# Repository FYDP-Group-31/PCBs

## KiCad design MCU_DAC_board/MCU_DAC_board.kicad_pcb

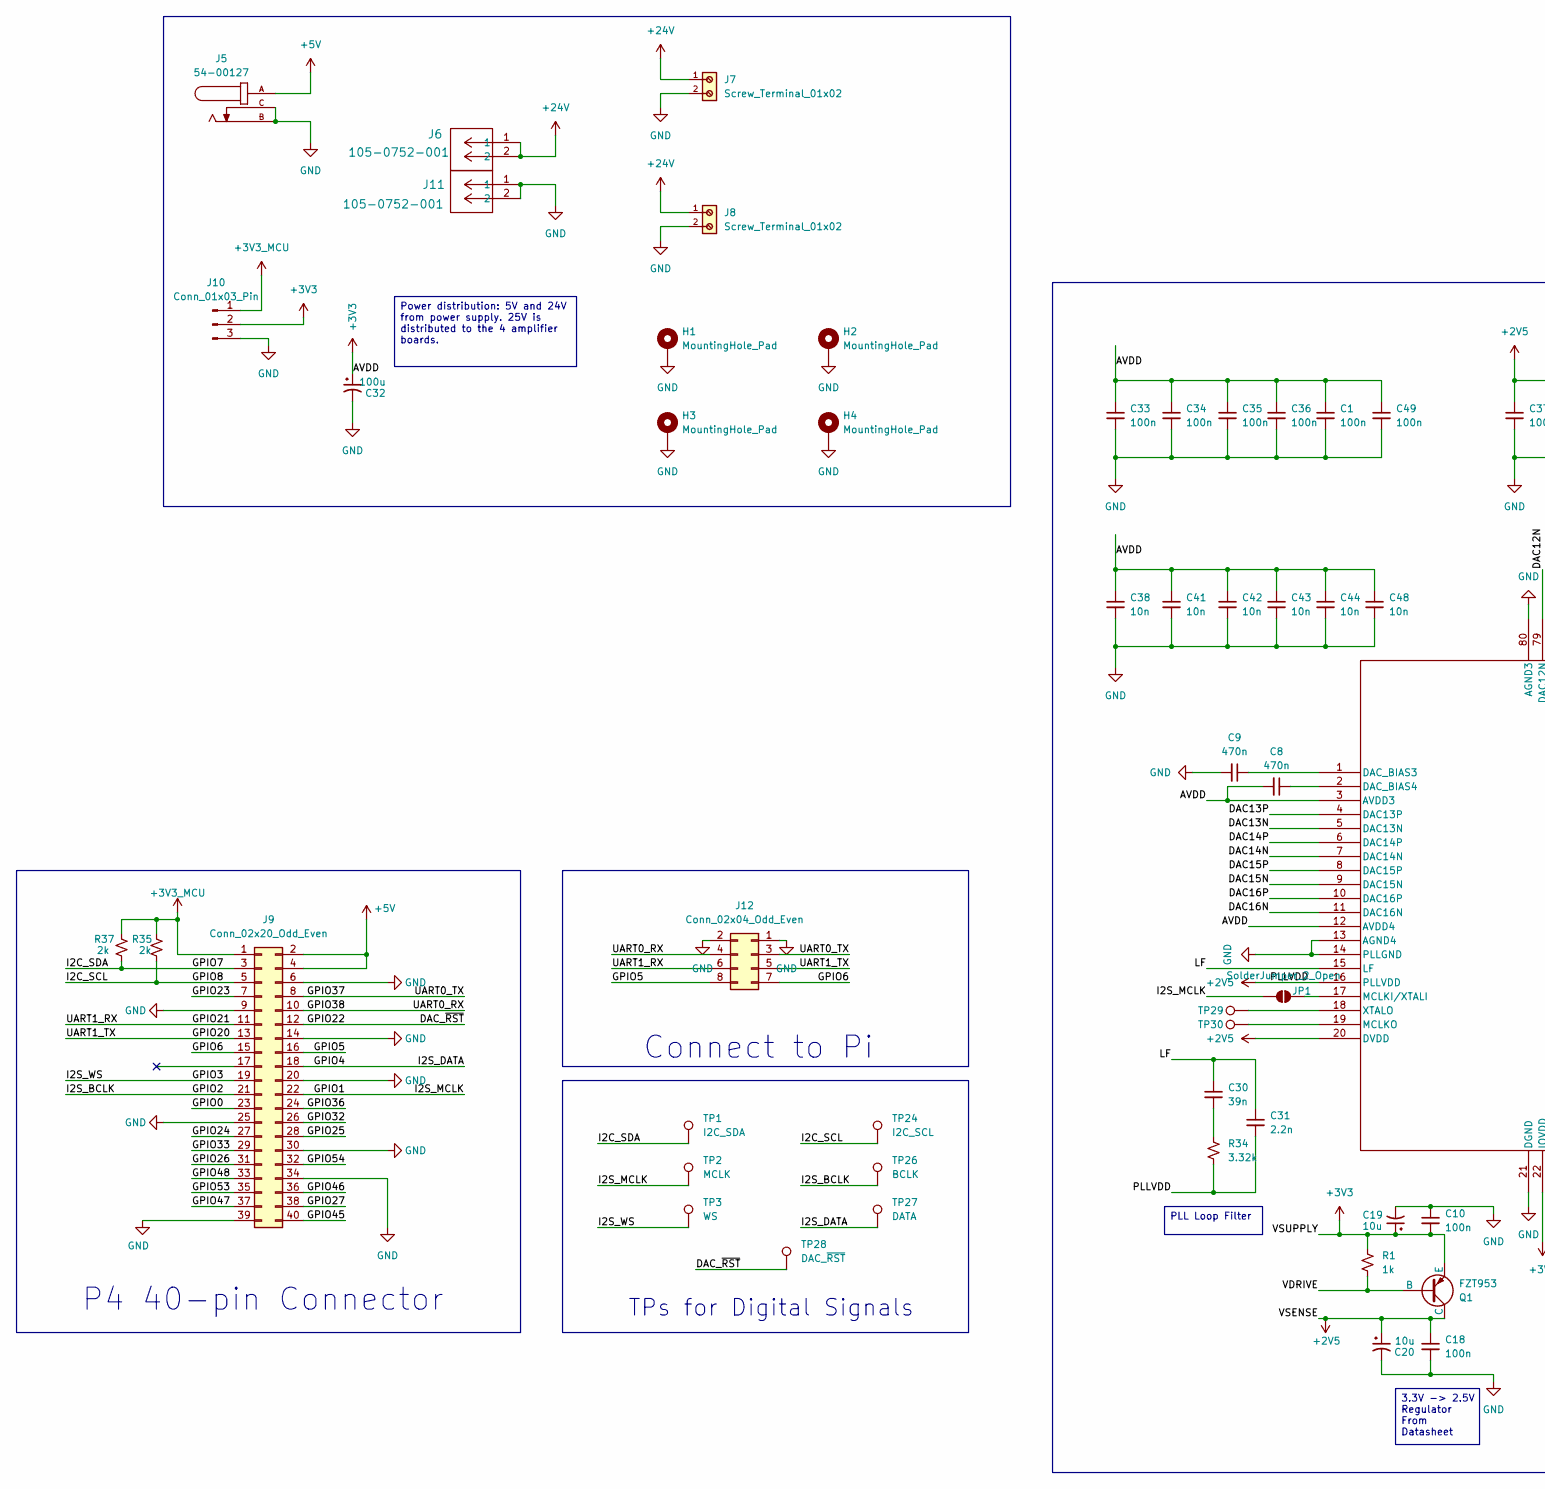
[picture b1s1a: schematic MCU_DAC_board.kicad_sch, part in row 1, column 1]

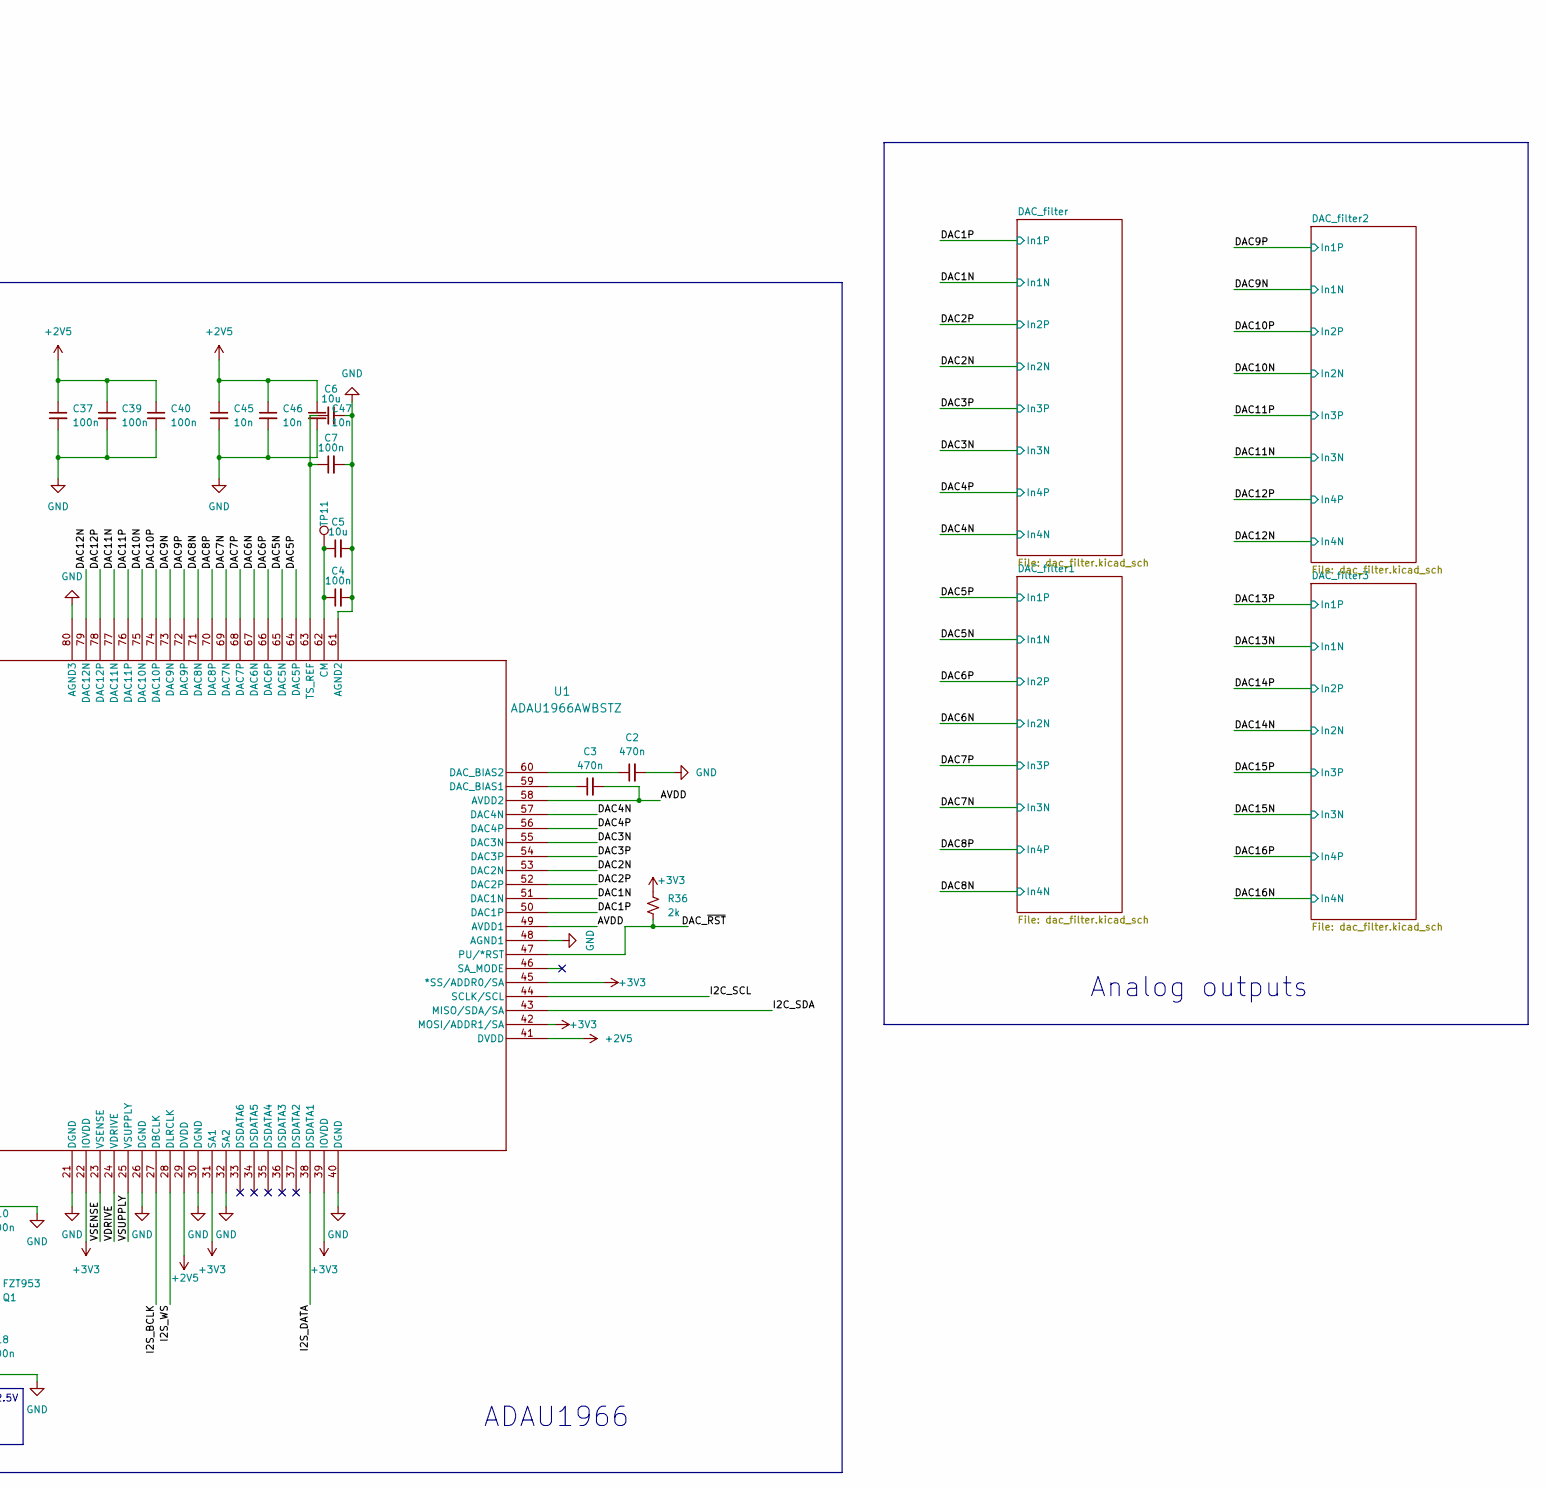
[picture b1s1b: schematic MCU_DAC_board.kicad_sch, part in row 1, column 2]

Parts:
C1, C4, C7, C10, C18, C33, C34, C35, C36, C37, C39, C40, C49: 100n; C_0603_1608Metric_Pad1.08x0.95mm_HandSolder
C2, C3, C8, C9: 470n; C_0603_1608Metric_Pad1.08x0.95mm_HandSolder
C5, C6: 10u; C_0805_2012Metric_Pad1.18x1.45mm_HandSolder
C19, C20: 10u; CP_Elec_4x4.5
C30: 39n; C_0805_2012Metric_Pad1.18x1.45mm_HandSolder
C31: 2.2n; C_0805_2012Metric_Pad1.18x1.45mm_HandSolder
C32: 100u; CP_Radial_D6.3mm_P2.50mm
C38, C41, C42, C43, C44, C45, C46, C47, C48: 10n; C_0603_1608Metric_Pad1.08x0.95mm_HandSolder
H1, H2, H3, H4: MountingHole_Pad; MountingHole_2.7mm_M2.5_DIN965_Pad_TopBottom
J5: 54-00127; TENSILITY_54-00127; PARTREV A
J6, J11: 105-0752-001; CONN_0752-001
J7, J8: Screw_Terminal_01x02; 691137710002
J9: Conn_02x20_Odd_Even; PinSocket_2x20_P2.54mm_Vertical_SMD
J10: Conn_01x03_Pin; PinHeader_1x03_P2.54mm_Vertical
J12: Conn_02x04_Odd_Even; PinSocket_2x04_P2.54mm_Vertical
JP1: SolderJumper_2_Open; R_0201_0603Metric_Pad0.64x0.40mm_HandSolder
Q1: FZT953; SOT-223-3_TabPin2
R1: 1k; R_0805_2012Metric_Pad1.20x1.40mm_HandSolder
R34: 3.32k; R_0805_2012Metric_Pad1.20x1.40mm_HandSolder
R35, R36, R37: 2k; R_0805_2012Metric_Pad1.20x1.40mm_HandSolder
TP1: I2C_SDA; TP_1.8x1mm
TP2: MCLK; TP_1.8x1mm
TP3: WS; TP_1.8x1mm
TP11: CM; TP_1.8x1mm
TP24: I2C_SCL; TP_1.8x1mm
TP26: BCLK; TP_1.8x1mm
TP27: DATA; TP_1.8x1mm
TP28: DAC_~{RST}; TP_1.8x1mm
TP29: XTALO; TP_1.8x1mm
TP30: MCLKO; TP_1.8x1mm
U1: ADAU1966AWBSTZ; ST_80_2_ADI

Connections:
+2V5: C18.1, C20.1, C31.2, C37.1, C39.1, C40.1, C45.1, C46.1, C47.1, Q1.2 (C), R34.2, U1.16 (PLLVDD), U1.20 (DVDD), U1.23 (VSENSE), U1.29 (DVDD), U1.41 (DVDD)
+3V3: C1.1, C3.2, C8.2, C10.2, C19.1, C32.1, C33.1, C34.1, C35.1, C36.1, C38.1, C41.1, C42.1, C43.1, C44.1, C48.1, C49.1, J10.2, Q1.3 (E), R1.1, R36.1, U1.3 (AVDD3), U1.12 (AVDD4), U1.22 (IOVDD), U1.25 (VSUPPLY), U1.31 (SA1), U1.39 (IOVDD), U1.42 (MOSI/ADDR1/SA), U1.45 (*SS/ADDR0/SA), U1.49 (AVDD1), U1.58 (AVDD2)
+3V3_MCU: J9.1, J10.1, R35.1, R37.1
+5V: J5.A, J9.2, J9.4
+24V: J6.1, J6.2, J7.1, J8.1
/DAC1N: U1.51 (DAC1N); also elsewhere on the board
/DAC1P: U1.50 (DAC1P); also elsewhere on the board
/DAC2N: U1.53 (DAC2N); also elsewhere on the board
/DAC2P: U1.52 (DAC2P); also elsewhere on the board
/DAC3N: U1.55 (DAC3N); also elsewhere on the board
/DAC3P: U1.54 (DAC3P); also elsewhere on the board
/DAC4N: U1.57 (DAC4N); also elsewhere on the board
/DAC4P: U1.56 (DAC4P); also elsewhere on the board
/DAC5N: U1.65 (DAC5N); also elsewhere on the board
/DAC5P: U1.64 (DAC5P); also elsewhere on the board
/DAC6N: U1.67 (DAC6N); also elsewhere on the board
/DAC6P: U1.66 (DAC6P); also elsewhere on the board
/DAC7N: U1.69 (DAC7N); also elsewhere on the board
/DAC7P: U1.68 (DAC7P); also elsewhere on the board
/DAC8N: U1.71 (DAC8N); also elsewhere on the board
/DAC8P: U1.70 (DAC8P); also elsewhere on the board
/DAC9N: U1.73 (DAC9N); also elsewhere on the board
/DAC9P: U1.72 (DAC9P); also elsewhere on the board
/DAC10N: U1.75 (DAC10N); also elsewhere on the board
/DAC10P: U1.74 (DAC10P); also elsewhere on the board
/DAC11N: U1.77 (DAC11N); also elsewhere on the board
/DAC11P: U1.76 (DAC11P); also elsewhere on the board
/DAC12N: U1.79 (DAC12N); also elsewhere on the board
/DAC12P: U1.78 (DAC12P); also elsewhere on the board
/DAC13N: U1.5 (DAC13N); also elsewhere on the board
/DAC13P: U1.4 (DAC13P); also elsewhere on the board
/DAC14N: U1.7 (DAC14N); also elsewhere on the board
/DAC14P: U1.6 (DAC14P); also elsewhere on the board
/DAC15N: U1.9 (DAC15N); also elsewhere on the board
/DAC15P: U1.8 (DAC15P); also elsewhere on the board
/DAC16N: U1.11 (DAC16N); also elsewhere on the board
/DAC16P: U1.10 (DAC16P); also elsewhere on the board
/DAC_~RST: J9.12, R36.2, TP28.1, U1.47 (PU/*RST)
/GPIO0: J9.23
/GPIO1: J9.22, JP1.1 (A), TP2.1
/GPIO2: J9.21, TP26.1, U1.27 (DBCLK)
/GPIO3: J9.19, TP3.1, U1.28 (DLRCLK)
/GPIO4: J9.18, TP27.1, U1.38 (DSDATA1)
/GPIO5: J9.16, J12.8
/GPIO6: J9.15, J12.7
/GPIO7: J9.3, R37.2, TP1.1, U1.43 (MISO/SDA/SA)
/GPIO8: J9.5, R35.2, TP24.1, U1.44 (SCLK/SCL)
/GPIO20: J9.13, J12.5
/GPIO21: J9.11, J12.6
/GPIO23: J9.7
/GPIO24: J9.27
/GPIO25: J9.28
/GPIO26: J9.31
/GPIO27: J9.38
/GPIO32: J9.26
/GPIO33: J9.29
/GPIO36: J9.24
/GPIO37: J9.8, J12.3
/GPIO38: J9.10, J12.4
/GPIO45: J9.40
/GPIO46: J9.36
/GPIO47: J9.37
/GPIO48: J9.33
/GPIO53: J9.35
/GPIO54: J9.32
/LF: C30.1, C31.1, U1.15 (LF)
/VDRIVE: Q1.1 (B), R1.2, U1.24 (VDRIVE)
GND: C1.2, C2.2, C4.2, C5.2, C6.2, C7.2, C9.2, C10.1, C18.2, C19.2, C20.2, C32.2, C33.2, C34.2, C35.2, C36.2, C37.2, C38.2, C39.2, C40.2, C41.2, C42.2, C43.2, C44.2, C45.2, C46.2, C47.2, C48.2, C49.2, H1.1, H2.1, H3.1, H4.1, J5.B, J5.C, J7.2, J8.2, J9.6, J9.9, J9.14, J9.20, J9.25, J9.30, J9.34, J9.39, J10.3, J11.1, J11.2, J12.1, J12.2, U1.13 (AGND4), U1.14 (PLLGND), U1.21 (DGND), U1.26 (DGND), U1.30 (DGND), U1.32 (SA2), U1.40 (DGND), U1.48 (AGND1), U1.61 (AGND2), U1.80 (AGND3)
unnamed: C30.2, R34.1
unnamed: JP1.2 (B), U1.17 (MCLKI/XTALI)
unnamed: C4.1, C5.1, TP11.1, U1.62 (CM)
unnamed: C3.1, U1.59 (DAC_BIAS1)
unnamed: C2.1, U1.60 (DAC_BIAS2)
unnamed: C9.1, U1.1 (DAC_BIAS3)
unnamed: C8.1, U1.2 (DAC_BIAS4)
unnamed: TP30.1, U1.19 (MCLKO)
unnamed: C6.1, C7.1, U1.63 (TS_REF)
unnamed: TP29.1, U1.18 (XTALO)

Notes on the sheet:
Connect to Pi
P4 40-pin Connector
Analog outputs
ADAU1966
TPs for Digital Signals
3.3V -> 2.5V Regulator From Datasheet
PLL Loop Filter
Power distribution: 5V and 24V from power supply. 25V is distributed to the 4 amplifier boards.

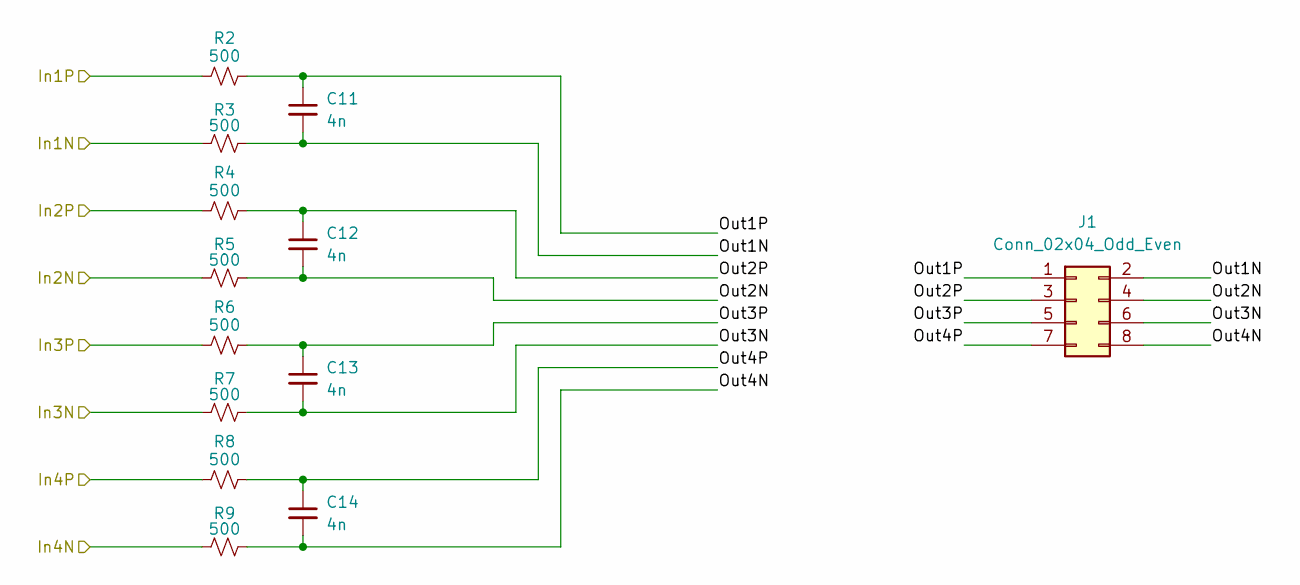
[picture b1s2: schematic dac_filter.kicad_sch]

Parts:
C11, C12, C13, C14: 4n; C_0805_2012Metric_Pad1.18x1.45mm_HandSolder
J1: Conn_02x04_Odd_Even; BHR-08-VUA
R2, R3, R4, R5, R6, R7, R8, R9: 500; R_0805_2012Metric_Pad1.20x1.40mm_HandSolder

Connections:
/DAC1N: R3.1; also elsewhere on the board
/DAC1P: R2.1; also elsewhere on the board
/DAC2N: R5.1; also elsewhere on the board
/DAC2P: R4.1; also elsewhere on the board
/DAC3N: R7.1; also elsewhere on the board
/DAC3P: R6.1; also elsewhere on the board
/DAC4N: R9.1; also elsewhere on the board
/DAC4P: R8.1; also elsewhere on the board
/DAC_filter/Out1N: C11.2, J1.2, R3.2
/DAC_filter/Out1P: C11.1, J1.1, R2.2
/DAC_filter/Out2N: C12.2, J1.4, R5.2
/DAC_filter/Out2P: C12.1, J1.3, R4.2
/DAC_filter/Out3N: C13.2, J1.6, R7.2
/DAC_filter/Out3P: C13.1, J1.5, R6.2
/DAC_filter/Out4N: C14.2, J1.8, R9.2
/DAC_filter/Out4P: C14.1, J1.7, R8.2

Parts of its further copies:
C15, C16, C17, C21, C22, C23, C24, C25, C26, C27, C28, C29: 4n; C_0805_2012Metric_Pad1.18x1.45mm_HandSolder
J2, J3, J4: Conn_02x04_Odd_Even; BHR-08-VUA
R10, R11, R12, R13, R14, R15, R16, R17, R18, R19, R20, R21, R22, R23, R24, R25, R26, R27, R28, R29, R30, R31, R32, R33: 500; R_0805_2012Metric_Pad1.20x1.40mm_HandSolder

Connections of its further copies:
/DAC5N: R11.1; also elsewhere on the board
/DAC5P: R10.1; also elsewhere on the board
/DAC6N: R13.1; also elsewhere on the board
/DAC6P: R12.1; also elsewhere on the board
/DAC7N: R15.1; also elsewhere on the board
/DAC7P: R14.1; also elsewhere on the board
/DAC8N: R17.1; also elsewhere on the board
/DAC8P: R16.1; also elsewhere on the board
/DAC9N: R19.1; also elsewhere on the board
/DAC9P: R18.1; also elsewhere on the board
/DAC10N: R21.1; also elsewhere on the board
/DAC10P: R20.1; also elsewhere on the board
/DAC11N: R23.1; also elsewhere on the board
/DAC11P: R22.1; also elsewhere on the board
/DAC12N: R25.1; also elsewhere on the board
/DAC12P: R24.1; also elsewhere on the board
/DAC13N: R27.1; also elsewhere on the board
/DAC13P: R26.1; also elsewhere on the board
/DAC14N: R29.1; also elsewhere on the board
/DAC14P: R28.1; also elsewhere on the board
/DAC15N: R31.1; also elsewhere on the board
/DAC15P: R30.1; also elsewhere on the board
/DAC16N: R33.1; also elsewhere on the board
/DAC16P: R32.1; also elsewhere on the board
/DAC_filter1/Out1N: C15.2, J2.2, R11.2
/DAC_filter1/Out1P: C15.1, J2.1, R10.2
/DAC_filter1/Out2N: C16.2, J2.4, R13.2
/DAC_filter1/Out2P: C16.1, J2.3, R12.2
/DAC_filter1/Out3N: C17.2, J2.6, R15.2
/DAC_filter1/Out3P: C17.1, J2.5, R14.2
/DAC_filter1/Out4N: C21.2, J2.8, R17.2
/DAC_filter1/Out4P: C21.1, J2.7, R16.2
/DAC_filter2/Out1N: C22.2, J3.2, R19.2
/DAC_filter2/Out1P: C22.1, J3.1, R18.2
/DAC_filter2/Out2N: C23.2, J3.4, R21.2
/DAC_filter2/Out2P: C23.1, J3.3, R20.2
/DAC_filter2/Out3N: C24.2, J3.6, R23.2
/DAC_filter2/Out3P: C24.1, J3.5, R22.2
/DAC_filter2/Out4N: C25.2, J3.8, R25.2
/DAC_filter2/Out4P: C25.1, J3.7, R24.2
/DAC_filter3/Out1N: C26.2, J4.2, R27.2
/DAC_filter3/Out1P: C26.1, J4.1, R26.2
/DAC_filter3/Out2N: C27.2, J4.4, R29.2
/DAC_filter3/Out2P: C27.1, J4.3, R28.2
/DAC_filter3/Out3N: C28.2, J4.6, R31.2
/DAC_filter3/Out3P: C28.1, J4.5, R30.2
/DAC_filter3/Out4N: C29.2, J4.8, R33.2
/DAC_filter3/Out4P: C29.1, J4.7, R32.2

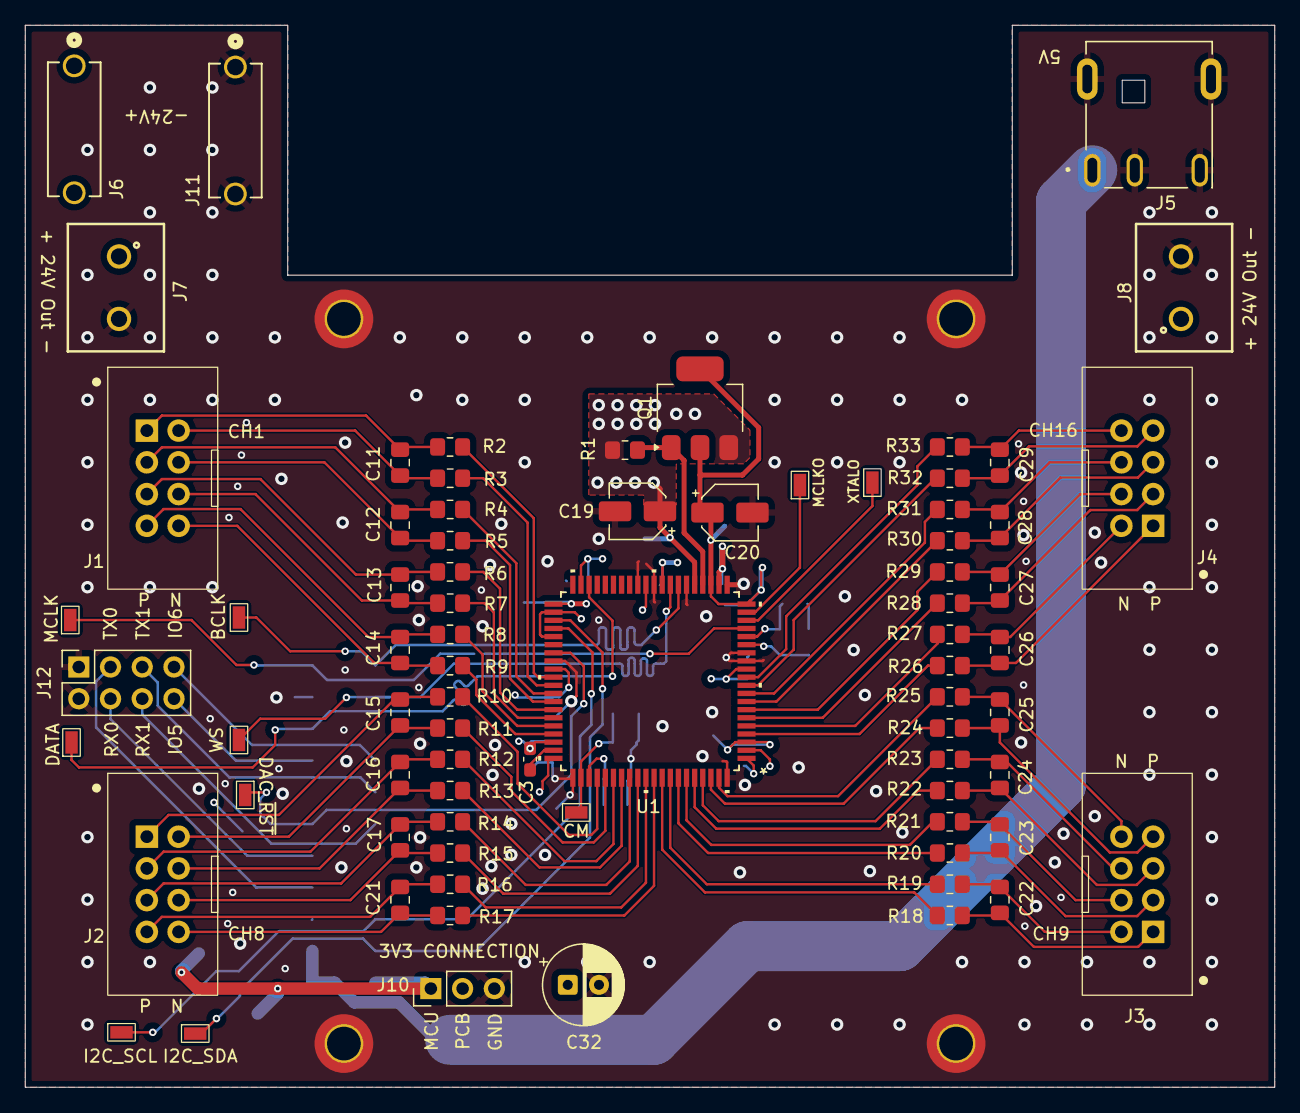
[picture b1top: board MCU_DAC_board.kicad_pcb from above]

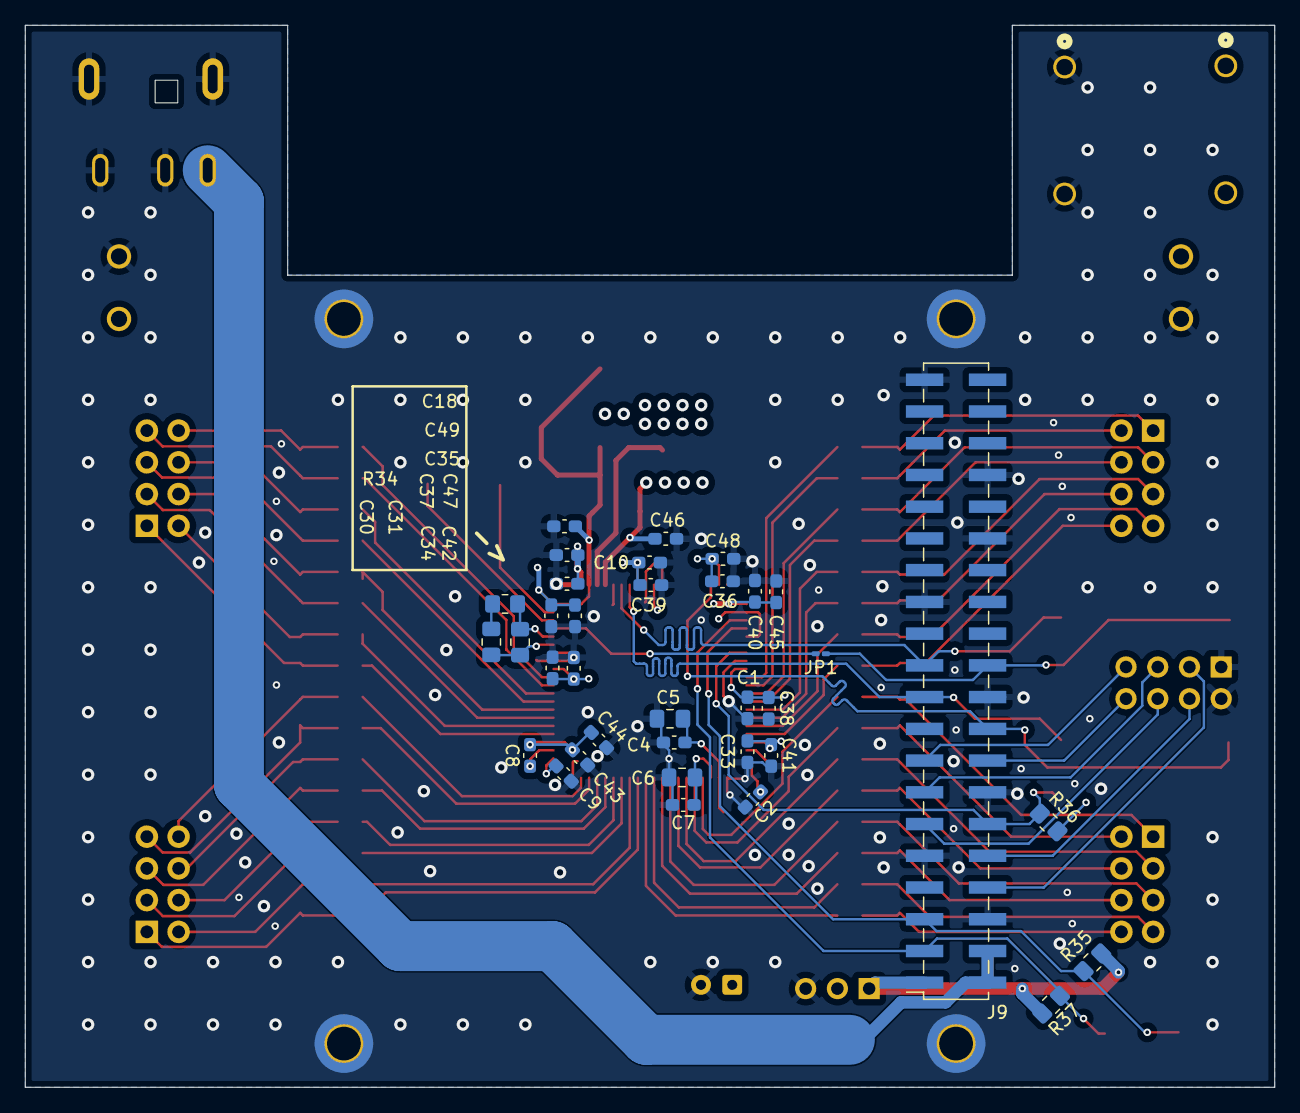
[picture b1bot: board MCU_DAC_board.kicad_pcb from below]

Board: 4 copper layers, 100.0 x 85.0 mm, 115 parts (35 on the bottom side), 95 nets.

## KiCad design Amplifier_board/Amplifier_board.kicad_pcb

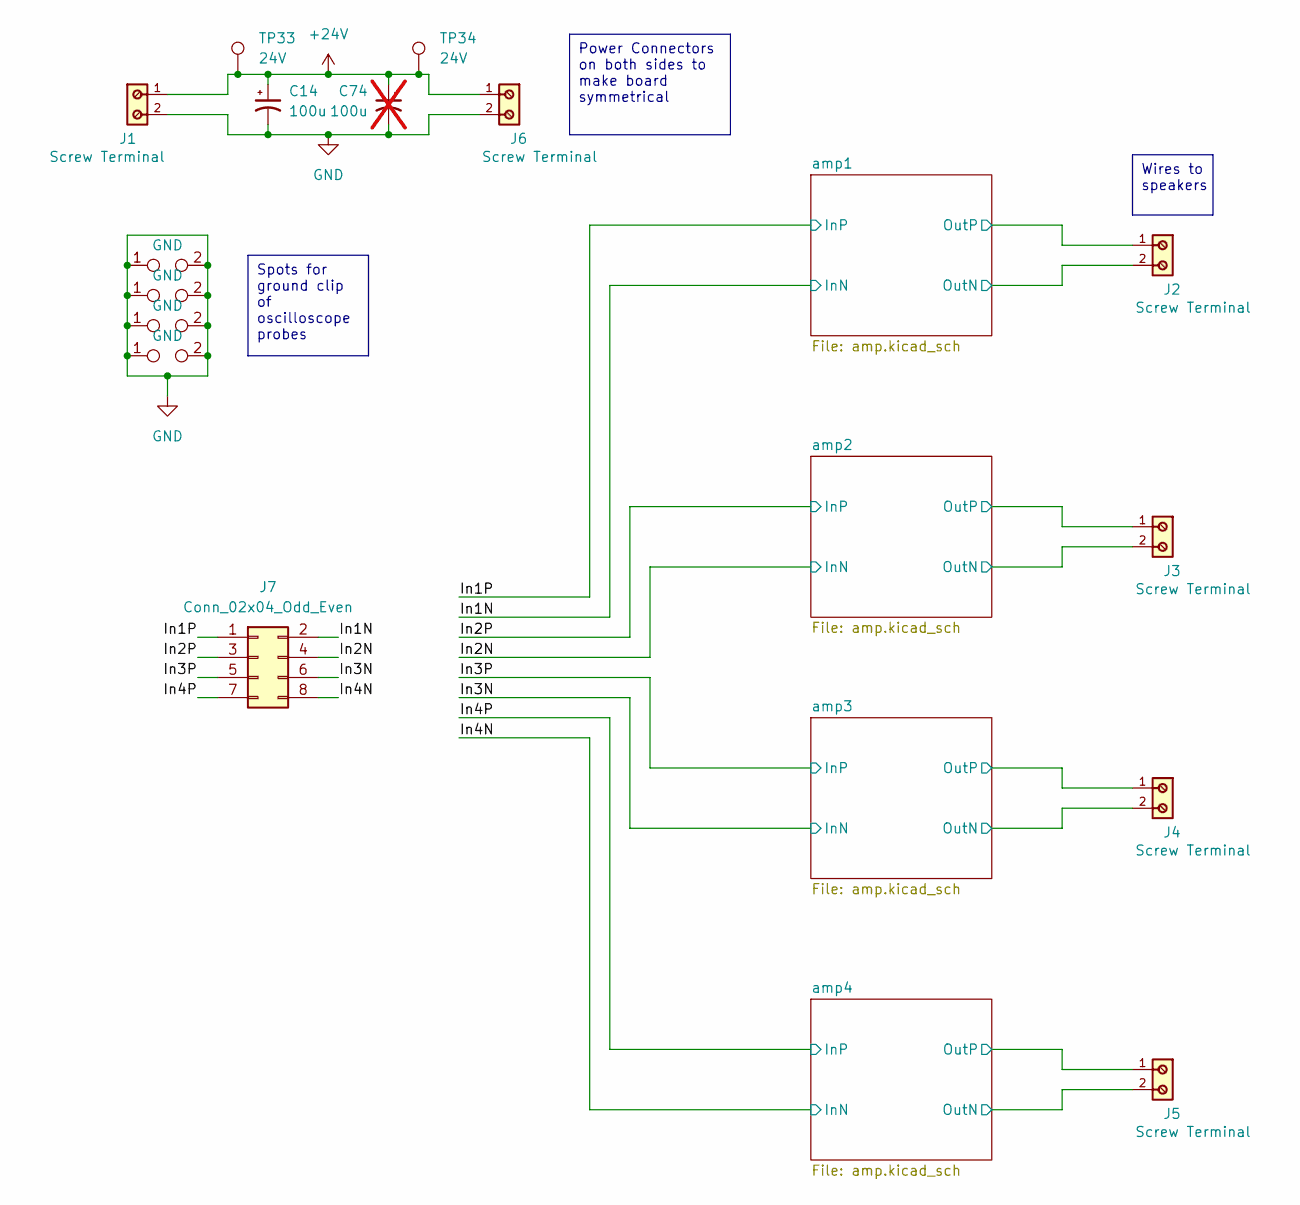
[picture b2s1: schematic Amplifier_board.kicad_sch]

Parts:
C14: 100u; CP_Radial_D6.3mm_P2.50mm
C74: 100u; CP_Radial_D6.3mm_P2.50mm; not fitted
J1, J2, J3, J4, J5, J6: Screw Terminal; 691137710002
J7: Conn_02x04_Odd_Even; BHR-08-VUA
TP33, TP34: 24V; TP_RCUCTE
TP35, TP36, TP37, TP38: GND; TestPoint_Bridge_Pitch5.08mm_Drill0.7mm

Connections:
+24V: C14.1, C74.1, J1.1, J6.1, TP33.1, TP34.1; also elsewhere on the board
/In1N: J7.2; also elsewhere on the board
/In1P: J7.1; also elsewhere on the board
/In2N: J7.4; also elsewhere on the board
/In2P: J7.3; also elsewhere on the board
/In3N: J7.6; also elsewhere on the board
/In3P: J7.5; also elsewhere on the board
/In4N: J7.8; also elsewhere on the board
/In4P: J7.7; also elsewhere on the board
/amp1/OutN: J2.2; also elsewhere on the board
/amp1/OutP: J2.1; also elsewhere on the board
/amp2/OutN: J3.2; also elsewhere on the board
/amp2/OutP: J3.1; also elsewhere on the board
/amp3/OutN: J4.2; also elsewhere on the board
/amp3/OutP: J4.1; also elsewhere on the board
/amp4/OutN: J5.2; also elsewhere on the board
/amp4/OutP: J5.1; also elsewhere on the board
GND: C14.2, C74.2, J1.2, J6.2, TP35.1, TP35.2, TP36.1, TP36.2, TP37.1, TP37.2, TP38.1, TP38.2; also elsewhere on the board

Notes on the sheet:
Wires to speakers
Spots for ground clip of oscilloscope probes
Power Connectors on both sides to make board symmetrical

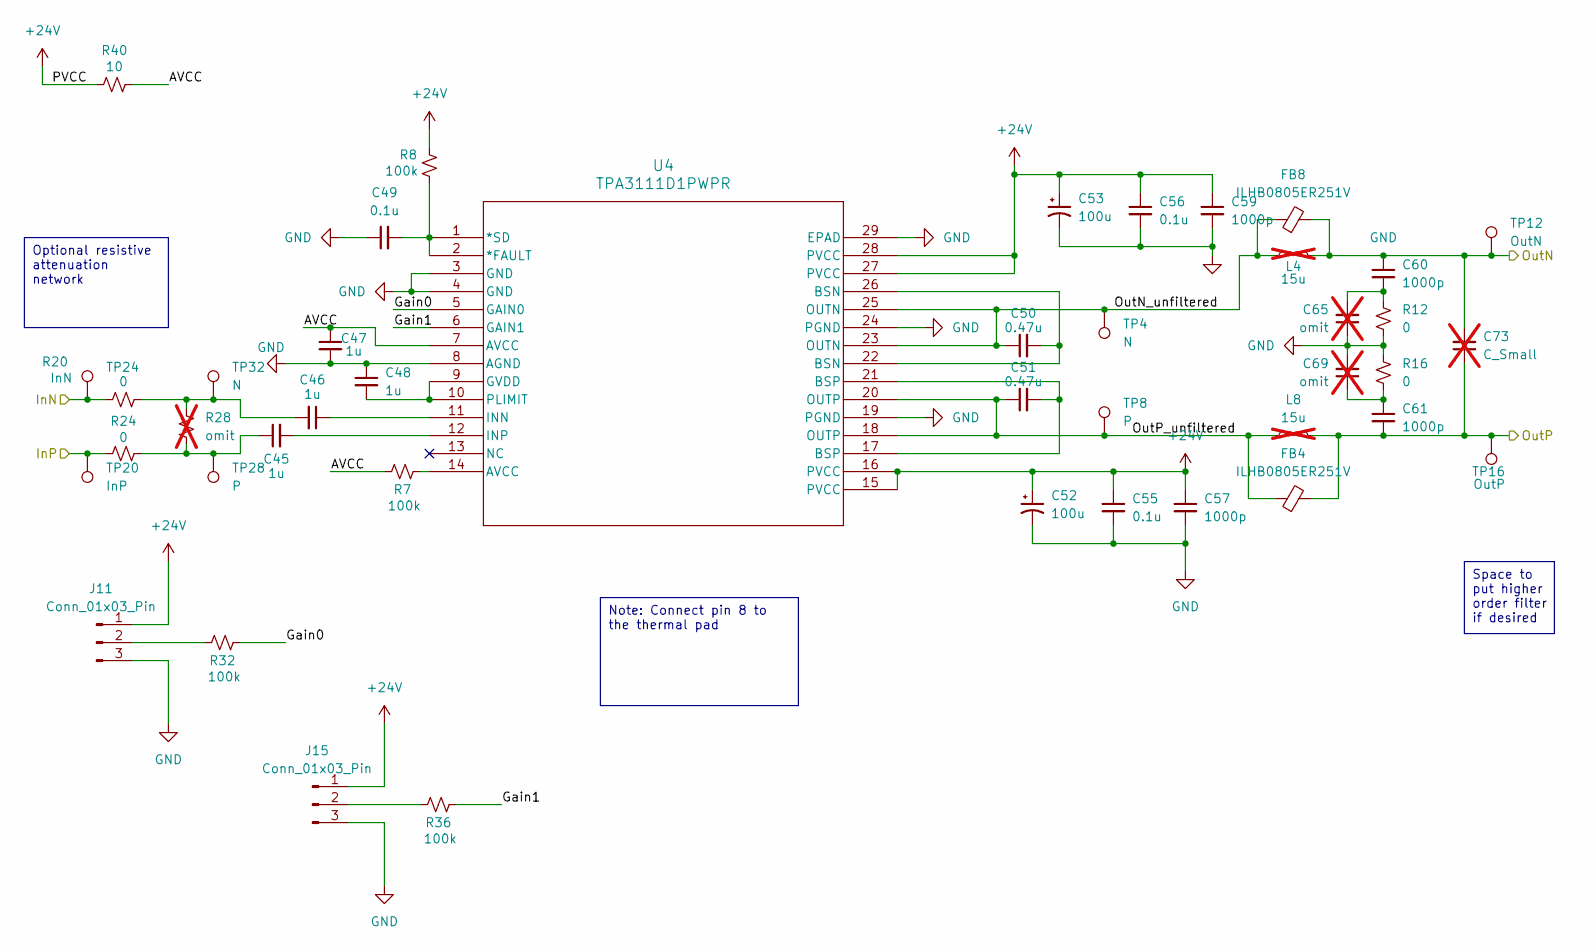
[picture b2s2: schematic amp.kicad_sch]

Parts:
C45, C46, C47, C48: 1u; C_0805_2012Metric_Pad1.18x1.45mm_HandSolder
C49, C55, C56: 0.1u; C_0805_2012Metric_Pad1.18x1.45mm_HandSolder
C50, C51: 0.47u; C_0805_2012Metric_Pad1.18x1.45mm_HandSolder
C52, C53: 100u; CP_Radial_D6.3mm_P2.50mm
C57, C59, C60, C61: 1000p; C_0805_2012Metric_Pad1.18x1.45mm_HandSolder
C65, C69: omit; C_0805_2012Metric_Pad1.18x1.45mm_HandSolder; not fitted
C73: C_Small; C_0805_2012Metric_Pad1.18x1.45mm_HandSolder; not fitted
FB4, FB8: ILHB0805ER251V; L_0805_2012Metric_Pad1.15x1.40mm_HandSolder
J11, J15: Conn_01x03_Pin; PinSocket_1x03_P2.54mm_Vertical
L4, L8: 15u; L_Taiyo-Yuden_NR-50xx_HandSoldering; not fitted
R7, R8, R32, R36: 100k; R_0805_2012Metric_Pad1.20x1.40mm_HandSolder
R12, R16, R20, R24: 0; R_0805_2012Metric_Pad1.20x1.40mm_HandSolder
R28: omit; R_0805_2012Metric_Pad1.20x1.40mm_HandSolder; not fitted
R40: 10; C_0805_2012Metric_Pad1.18x1.45mm_HandSolder
TP4, TP32: N; TP_RCUCTE
TP8, TP28: P; TP_RCUCTE
TP12: OutN; TP_RCUCTE
TP16: OutP; TP_RCUCTE
TP20: InP; TP_RCUCTE
TP24: InN; TP_RCUCTE
U4: TPA3111D1PWPR; PWP28_6P17X2P4

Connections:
+24V: C52.1, C53.1, C55.1, C56.1, C57.1, C59.1, J11.1, J15.1, R8.1, R40.1, U4.15 (PVCC), U4.16 (PVCC), U4.27 (PVCC), U4.28 (PVCC); also elsewhere on the board
/In4N: R20.2, TP24.1; also elsewhere on the board
/In4P: R24.2, TP20.1; also elsewhere on the board
/amp4/AVCC: C47.1, R7.1, R40.2, U4.7 (AVCC)
/amp4/Gain0: R32.2, U4.5 (GAIN0)
/amp4/Gain1: R36.2, U4.6 (GAIN1)
/amp4/OutN: C60.1, C73.2, FB8.2, L4.2, TP12.1; also elsewhere on the board
/amp4/OutN_unfiltered: C50.1, FB8.1, L4.1, TP4.1, U4.23 (OUTN), U4.25 (OUTN)
/amp4/OutP: C61.2, C73.1, FB4.2, L8.2, TP16.1; also elsewhere on the board
/amp4/OutP_unfiltered: C51.1, FB4.1, L8.1, TP8.1, U4.18 (OUTP), U4.20 (OUTP)
GND: C47.2, C48.1, C49.1, C52.2, C53.2, C55.2, C56.2, C57.2, C59.2, C65.1, C69.2, J11.3, J15.3, R12.1, R16.2, U4.3 (GND), U4.4 (GND), U4.8 (AGND), U4.19 (PGND), U4.24 (PGND), U4.29 (EPAD); also elsewhere on the board
unnamed: C45.1, R24.1, R28.2, TP28.1
unnamed: C46.2, R20.1, R28.1, TP32.1
unnamed: C50.2, U4.22 (BSN), U4.26 (BSN)
unnamed: C51.2, U4.17 (BSP), U4.21 (BSP)
unnamed: C60.2, C65.2, R12.2
unnamed: C61.1, C69.1, R16.1
unnamed: J11.2, R32.1
unnamed: J15.2, R36.1
unnamed: R7.2, U4.14 (AVCC)
unnamed: C49.2, R8.2, U4.1 (*SD), U4.2 (*FAULT)
unnamed: C48.2, U4.9 (GVDD), U4.10 (PLIMIT)
unnamed: C46.1, U4.11 (INN)
unnamed: C45.2, U4.12 (INP)

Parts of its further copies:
C1, C2, C3, C4, C15, C16, C17, C18, C30, C31, C32, C33: 1u; C_0805_2012Metric_Pad1.18x1.45mm_HandSolder
C5, C10, C11, C19, C24, C25, C34, C39, C40: 0.1u; C_0805_2012Metric_Pad1.18x1.45mm_HandSolder
C6, C7, C20, C21, C35, C36: 0.47u; C_0805_2012Metric_Pad1.18x1.45mm_HandSolder
C8, C9, C22, C23, C37, C38: 100u; CP_Radial_D6.3mm_P2.50mm
C12, C13, C26, C27, C28, C29, C41, C42, C43, C44, C54, C58: 1000p; C_0805_2012Metric_Pad1.18x1.45mm_HandSolder
C62, C63, C64, C66, C67, C68: omit; C_0805_2012Metric_Pad1.18x1.45mm_HandSolder; not fitted
C70, C71, C72: C_Small; C_0805_2012Metric_Pad1.18x1.45mm_HandSolder; not fitted
FB1, FB2, FB3, FB5, FB6, FB7: ILHB0805ER251V; L_0805_2012Metric_Pad1.15x1.40mm_HandSolder
J8, J9, J10, J12, J13, J14: Conn_01x03_Pin; PinSocket_1x03_P2.54mm_Vertical
L1, L2, L3, L5, L6, L7: 15u; L_Taiyo-Yuden_NR-50xx_HandSoldering; not fitted
R1, R2, R3, R4, R5, R6, R29, R30, R31, R33, R34, R35: 100k; R_0805_2012Metric_Pad1.20x1.40mm_HandSolder
R9, R10, R11, R13, R14, R15, R17, R18, R19, R21, R22, R23: 0; R_0805_2012Metric_Pad1.20x1.40mm_HandSolder
R25, R26, R27: omit; R_0805_2012Metric_Pad1.20x1.40mm_HandSolder; not fitted
R37, R38, R39: 10; C_0805_2012Metric_Pad1.18x1.45mm_HandSolder
TP1, TP2, TP3, TP29, TP30, TP31: N; TP_RCUCTE
TP5, TP6, TP7, TP25, TP26, TP27: P; TP_RCUCTE
TP9, TP10, TP11: OutN; TP_RCUCTE
TP13, TP14, TP15: OutP; TP_RCUCTE
TP17, TP18, TP19: InP; TP_RCUCTE
TP21, TP22, TP23: InN; TP_RCUCTE
U1, U2, U3: TPA3111D1PWPR; PWP28_6P17X2P4

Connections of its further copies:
+24V: C8.1, C9.1, C10.1, C11.1, C12.1, C13.1, C22.1, C23.1, C24.1, C25.1, C26.1, C27.1, C37.1, C38.1, C39.1, C40.1, C41.1, C42.1, J8.1, J9.1, J10.1, J12.1, J13.1, J14.1, R2.1, R4.1, R6.1, R37.1, R38.1, R39.1, U1.15 (PVCC), U1.16 (PVCC), U1.27 (PVCC), U1.28 (PVCC), U2.15 (PVCC), U2.16 (PVCC), U2.27 (PVCC), U2.28 (PVCC), U3.15 (PVCC), U3.16 (PVCC), U3.27 (PVCC), U3.28 (PVCC); also elsewhere on the board
/In1N: R17.2, TP21.1; also elsewhere on the board
/In1P: R21.2, TP17.1; also elsewhere on the board
/In2N: R18.2, TP22.1; also elsewhere on the board
/In2P: R22.2, TP18.1; also elsewhere on the board
/In3N: R19.2, TP23.1; also elsewhere on the board
/In3P: R23.2, TP19.1; also elsewhere on the board
/amp1/AVCC: C3.1, R1.1, R37.2, U1.7 (AVCC)
/amp1/Gain0: R29.2, U1.5 (GAIN0)
/amp1/Gain1: R33.2, U1.6 (GAIN1)
/amp1/OutN: C54.1, C70.2, FB5.2, L1.2, TP9.1; also elsewhere on the board
/amp1/OutN_unfiltered: C6.1, FB5.1, L1.1, TP1.1, U1.23 (OUTN), U1.25 (OUTN)
/amp1/OutP: C58.2, C70.1, FB1.2, L5.2, TP13.1; also elsewhere on the board
/amp1/OutP_unfiltered: C7.1, FB1.1, L5.1, TP5.1, U1.18 (OUTP), U1.20 (OUTP)
/amp2/AVCC: C17.1, R3.1, R38.2, U2.7 (AVCC)
/amp2/Gain0: R30.2, U2.5 (GAIN0)
/amp2/Gain1: R34.2, U2.6 (GAIN1)
/amp2/OutN: C28.1, C71.2, FB6.2, L2.2, TP10.1; also elsewhere on the board
/amp2/OutN_unfiltered: C20.1, FB6.1, L2.1, TP2.1, U2.23 (OUTN), U2.25 (OUTN)
/amp2/OutP: C29.2, C71.1, FB2.2, L6.2, TP14.1; also elsewhere on the board
/amp2/OutP_unfiltered: C21.1, FB2.1, L6.1, TP6.1, U2.18 (OUTP), U2.20 (OUTP)
/amp3/AVCC: C32.1, R5.1, R39.2, U3.7 (AVCC)
/amp3/Gain0: R31.2, U3.5 (GAIN0)
/amp3/Gain1: R35.2, U3.6 (GAIN1)
/amp3/OutN: C43.1, C72.2, FB7.2, L3.2, TP11.1; also elsewhere on the board
/amp3/OutN_unfiltered: C35.1, FB7.1, L3.1, TP3.1, U3.23 (OUTN), U3.25 (OUTN)
/amp3/OutP: C44.2, C72.1, FB3.2, L7.2, TP15.1; also elsewhere on the board
/amp3/OutP_unfiltered: C36.1, FB3.1, L7.1, TP7.1, U3.18 (OUTP), U3.20 (OUTP)
GND: C3.2, C4.1, C5.1, C8.2, C9.2, C10.2, C11.2, C12.2, C13.2, C17.2, C18.1, C19.1, C22.2, C23.2, C24.2, C25.2, C26.2, C27.2, C32.2, C33.1, C34.1, C37.2, C38.2, C39.2, C40.2, C41.2, C42.2, C62.1, C63.1, C64.1, C66.2, C67.2, C68.2, J8.3, J9.3, J10.3, J12.3, J13.3, J14.3, R9.1, R10.1, R11.1, R13.2, R14.2, R15.2, U1.3 (GND), U1.4 (GND), U1.8 (AGND), U1.19 (PGND), U1.24 (PGND), U1.29 (EPAD), U2.3 (GND), U2.4 (GND), U2.8 (AGND), U2.19 (PGND), U2.24 (PGND), U2.29 (EPAD), U3.3 (GND), U3.4 (GND), U3.8 (AGND), U3.19 (PGND), U3.24 (PGND), U3.29 (EPAD); also elsewhere on the board
unnamed: C1.1, R21.1, R25.2, TP25.1
unnamed: C2.2, R17.1, R25.1, TP29.1
unnamed: C6.2, U1.22 (BSN), U1.26 (BSN)
unnamed: C7.2, U1.17 (BSP), U1.21 (BSP)
unnamed: C15.1, R22.1, R26.2, TP26.1
unnamed: C16.2, R18.1, R26.1, TP30.1
unnamed: C20.2, U2.22 (BSN), U2.26 (BSN)
unnamed: C21.2, U2.17 (BSP), U2.21 (BSP)
unnamed: C28.2, C63.2, R10.2
unnamed: C29.1, C67.1, R14.1
unnamed: C30.1, R23.1, R27.2, TP27.1
unnamed: C31.2, R19.1, R27.1, TP31.1
unnamed: C35.2, U3.22 (BSN), U3.26 (BSN)
unnamed: C36.2, U3.17 (BSP), U3.21 (BSP)
unnamed: C43.2, C64.2, R11.2
unnamed: C44.1, C68.1, R15.1
unnamed: C54.2, C62.2, R9.2
unnamed: C58.1, C66.1, R13.1
unnamed: J8.2, R29.1
unnamed: J9.2, R30.1
unnamed: J10.2, R31.1
unnamed: J12.2, R33.1
unnamed: J13.2, R34.1
unnamed: J14.2, R35.1
unnamed: R1.2, U1.14 (AVCC)
unnamed: R3.2, U2.14 (AVCC)
unnamed: R5.2, U3.14 (AVCC)
unnamed: C5.2, R2.2, U1.1 (*SD), U1.2 (*FAULT)
unnamed: C4.2, U1.9 (GVDD), U1.10 (PLIMIT)
unnamed: C2.1, U1.11 (INN)
unnamed: C1.2, U1.12 (INP)
unnamed: C19.2, R4.2, U2.1 (*SD), U2.2 (*FAULT)
unnamed: C18.2, U2.9 (GVDD), U2.10 (PLIMIT)
unnamed: C16.1, U2.11 (INN)
unnamed: C15.2, U2.12 (INP)
unnamed: C34.2, R6.2, U3.1 (*SD), U3.2 (*FAULT)
unnamed: C33.2, U3.9 (GVDD), U3.10 (PLIMIT)
unnamed: C31.1, U3.11 (INN)
unnamed: C30.2, U3.12 (INP)

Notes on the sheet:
Optional resistive attenuation network
Note: Connect pin 8 to the thermal pad
Space to put higher order filter if desired
